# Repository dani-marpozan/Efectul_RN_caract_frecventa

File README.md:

# Eefectul reactiei negative asupra caracteristicii de frecventa

Model 3D

## Schematic

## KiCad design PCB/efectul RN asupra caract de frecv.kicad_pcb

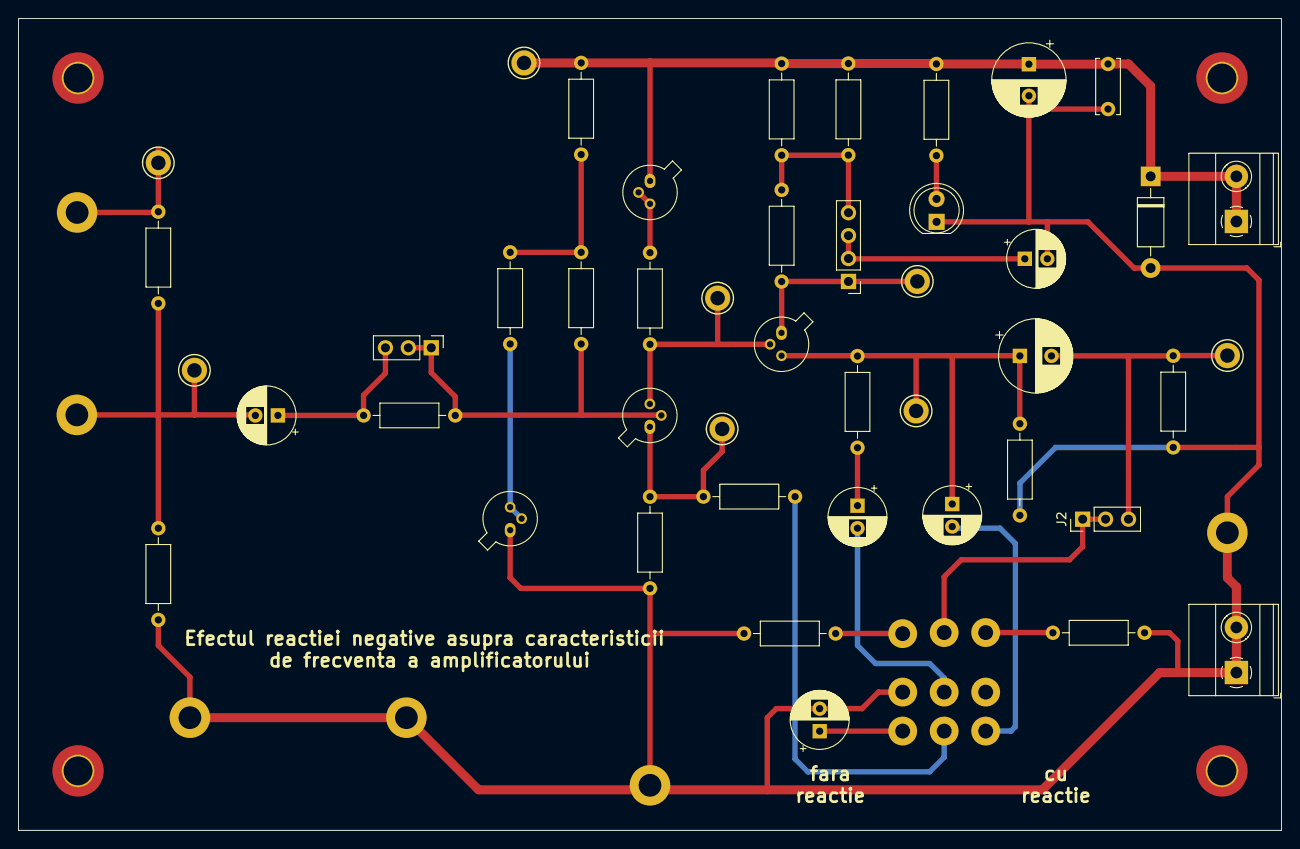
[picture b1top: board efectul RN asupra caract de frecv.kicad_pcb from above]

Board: 2 copper layers, 140.0 x 90.0 mm, 56 parts (0 on the bottom side), 25 nets.

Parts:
C1, C2, C3, C4, C6: 22uF; CP_Radial_D6.3mm_P2.50mm
C5: 100uF; CP_Radial_D8.0mm_P3.50mm
C7: 770nF; C_Disc_D6.0mm_W2.5mm_P5.00mm
C8: 330uF; CP_Radial_D8.0mm_P3.50mm
D1: LED; LED_D5.0mm
D2: 1N4001; D_DO-41_SOD81_P10.16mm_Horizontal
H1, H2, H3, H4: MountingHole; MountingHole_3.2mm_M3_ISO7380_Pad_TopBottom
J1, J2: Conn_01x03_Pin; PinHeader_1x03_P2.54mm_Vertical
J3: Conn_01x04_Pin; PinHeader_1x04_P2.54mm_Vertical
J4, J5: Screw_Terminal_01x02; TerminalBlock_Phoenix_MKDS-1,5-2_1x02_P5.00mm_Horizontal
J6, J7: Conn_01x01_Male; TestPoint
Q1, Q3: BCY59; TO-18-3
Q2, Q4: BCY79; TO-18-3
R0XA1: 1.8k; R_Axial_DIN0207_L6.3mm_D2.5mm_P10.16mm_Horizontal
R0XR1: 133; R_Axial_DIN0207_L6.3mm_D2.5mm_P10.16mm_Horizontal
R1: 18k; R_Axial_DIN0207_L6.3mm_D2.5mm_P10.16mm_Horizontal
R2, R9, R11: 2.2k; R_Axial_DIN0207_L6.3mm_D2.5mm_P10.16mm_Horizontal
R3: 100k; R_Axial_DIN0207_L6.3mm_D2.5mm_P10.16mm_Horizontal
R4: 2k; R_Axial_DIN0207_L6.3mm_D2.5mm_P10.16mm_Horizontal
R5: 20k; R_Axial_DIN0207_L6.3mm_D2.5mm_P10.16mm_Horizontal
R6, R81, R82: 15k; R_Axial_DIN0207_L6.3mm_D2.5mm_P10.16mm_Horizontal
R7: 100; R_Axial_DIN0207_L6.3mm_D2.5mm_P10.16mm_Horizontal
R10: 22k; R_Axial_DIN0207_L6.3mm_D2.5mm_P10.16mm_Horizontal
R12: 22; R_Axial_DIN0207_L6.3mm_D2.5mm_P10.16mm_Horizontal
R13: 5 k; R_Axial_DIN0207_L6.3mm_D2.5mm_P10.16mm_Horizontal
RL1: 300k; R_Axial_DIN0207_L6.3mm_D2.5mm_P10.16mm_Horizontal
Rix1: 56k; R_Axial_DIN0207_L6.3mm_D2.5mm_P10.16mm_Horizontal
S1: GF-161-0005
TP1, TP2, TP3, TP4: TestPoint
TP5, TP6, TP7, TP8, TP9, TP10, TP11, TP12: TestPoint; Kesytone TP Multipurpose 5013

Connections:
+24V: C7.2, C8.1, D2.1 (K), J4.1, J4.2, Q4.1 (E), R1.2, R13.1, R81.2, R82.2, TP8.1
GND: C3.2, C6.2, C7.1, C8.2, D1.1 (K), D2.2 (A), J5.1, J5.2, Q3.1 (E), R0XA1.1, R0XR1.1, R4.1, R9.1, R12.2, RL1.2, S1.6, TP1.1, TP2.1, TP3.1, TP4.1
IN1: J6.1, R11.1, TP7.1
IN2: C1.2, J7.1, R11.2, R12.1, TP6.1
unnamed: C2.2, S1.1
unnamed: C3.1, S1.3
unnamed: C4.1, R10.1
unnamed: C4.2, S1.5
unnamed: D1.2 (A), R13.2
unnamed: J1.1, J1.2, Q1.2 (B), R3.1, Rix1.2
unnamed: C1.1, J1.3, Rix1.1
unnamed: J2.1, J2.2, S1.8
unnamed: C5.2, J2.3, RL1.1, TP5.1
unnamed: J3.1, Q2.1 (E), R7.1, TP10.1
unnamed: C6.1, J3.2, J3.3
unnamed: J3.4, R7.2, R81.1, R82.1
unnamed: Q1.3 (C), Q2.2 (B), R6.1, TP11.1
unnamed: Q1.1 (E), R4.2, R5.2, TP12.1
unnamed: C2.1, C5.1, Q2.3 (C), R9.2, R10.2, TP9.1
unnamed: Q3.2 (B), Q3.3 (C), R2.1
unnamed: Q4.2 (B), Q4.3 (C), R6.2
unnamed: R0XA1.2, S1.9
unnamed: R0XR1.2, S1.7
unnamed: R1.1, R2.2, R3.2
unnamed: R5.1, S1.2
